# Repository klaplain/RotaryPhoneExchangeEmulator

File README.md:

# RotaryPhoneExchangeEmulator
This system simulates a telephone exchange connected to a rotary phone.  It provides the dial tone and ring tone.  When the user dials a number, it plays back an MP3 file stored on the SD card.  A call can also be initiated from an IR remote control.  This causes the phone to ring and when the user picks up, plays the requested sound file.

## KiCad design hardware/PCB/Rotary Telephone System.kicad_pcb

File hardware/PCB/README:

This PCB was developed using KiCAD but hasn't yet been proven

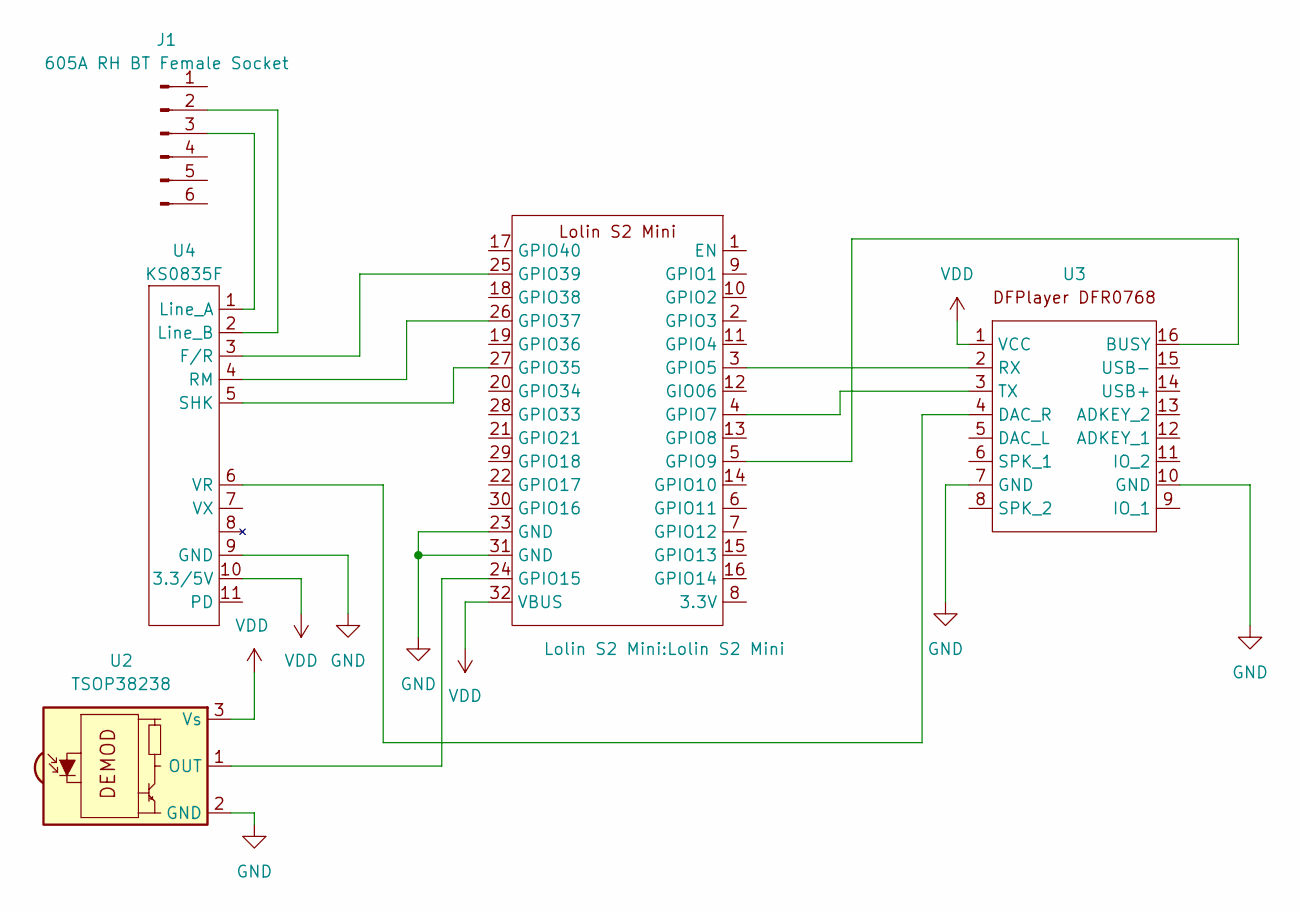
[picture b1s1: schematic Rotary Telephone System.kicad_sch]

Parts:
J1: 605A RH BT Female Socket; 605A BT Female PCB Socket
U1: Lolin S2 Mini
U2: TSOP38238; Vishay_MINICAST-3Pin
U3: DFR0768-mp3-player
U4: KS0835F

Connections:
GND: U1.23 (GND), U1.31 (GND), U2.2 (GND), U3.7 (GND), U3.10 (GND), U4.9 (GND)
unnamed: J1.2, U4.2 (Line_B)
unnamed: J1.3, U4.1 (Line_A)
unnamed: U1.3 (GPIO5), U3.2 (RX)
unnamed: U1.4 (GPIO7), U3.3 (TX)
unnamed: U1.5 (GPIO9), U3.16 (BUSY)
unnamed: U1.24 (GPIO15), U2.1 (OUT)
unnamed: U1.27 (GPIO35), U4.5 (SHK)
unnamed: U1.26 (GPIO37), U4.4 (RM)
unnamed: U1.25 (GPIO39), U4.3 (F/R)
unnamed: U3.4 (DAC_R), U4.6 (VR)
VDD: U1.32 (VBUS), U2.3 (Vs), U3.1 (VCC), U4.10 (3.3/5V)

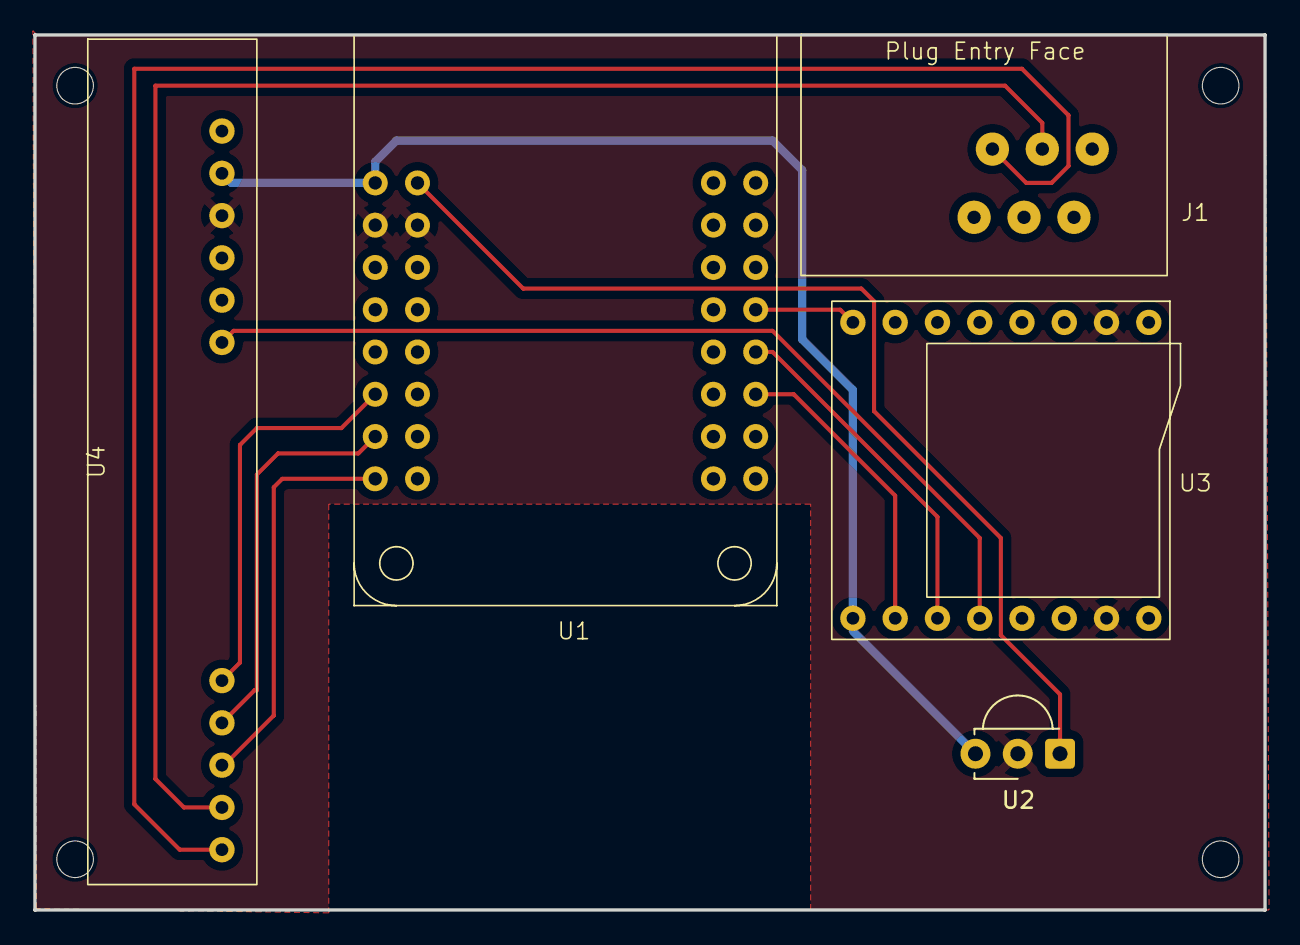
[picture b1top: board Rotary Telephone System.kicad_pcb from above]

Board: 2 copper layers, 73.9 x 52.6 mm, 5 parts (0 on the bottom side), 12 nets.

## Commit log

2025-10-20 Add README with project description
2025-10-20 Bill of Materials for hardware components
2025-10-20 README for PCB development using KiCAD
2025-10-20 Update README with required libraries
    Added information about required libraries for the code.
2025-10-20 Add infrared remote control entry to BOM
    Added entry for using an old RCA TV remote control.
2025-10-20 DFPlayer Telephone Numbers and Presets
2025-10-20 Add files via upload
    Describes the phone state machine
2025-10-20 Add KS0835F RING SLIC to BOM with reference link
2025-10-20 Required and optional sound files
    These files need to be copied to the SD card in the directory structure provided here
